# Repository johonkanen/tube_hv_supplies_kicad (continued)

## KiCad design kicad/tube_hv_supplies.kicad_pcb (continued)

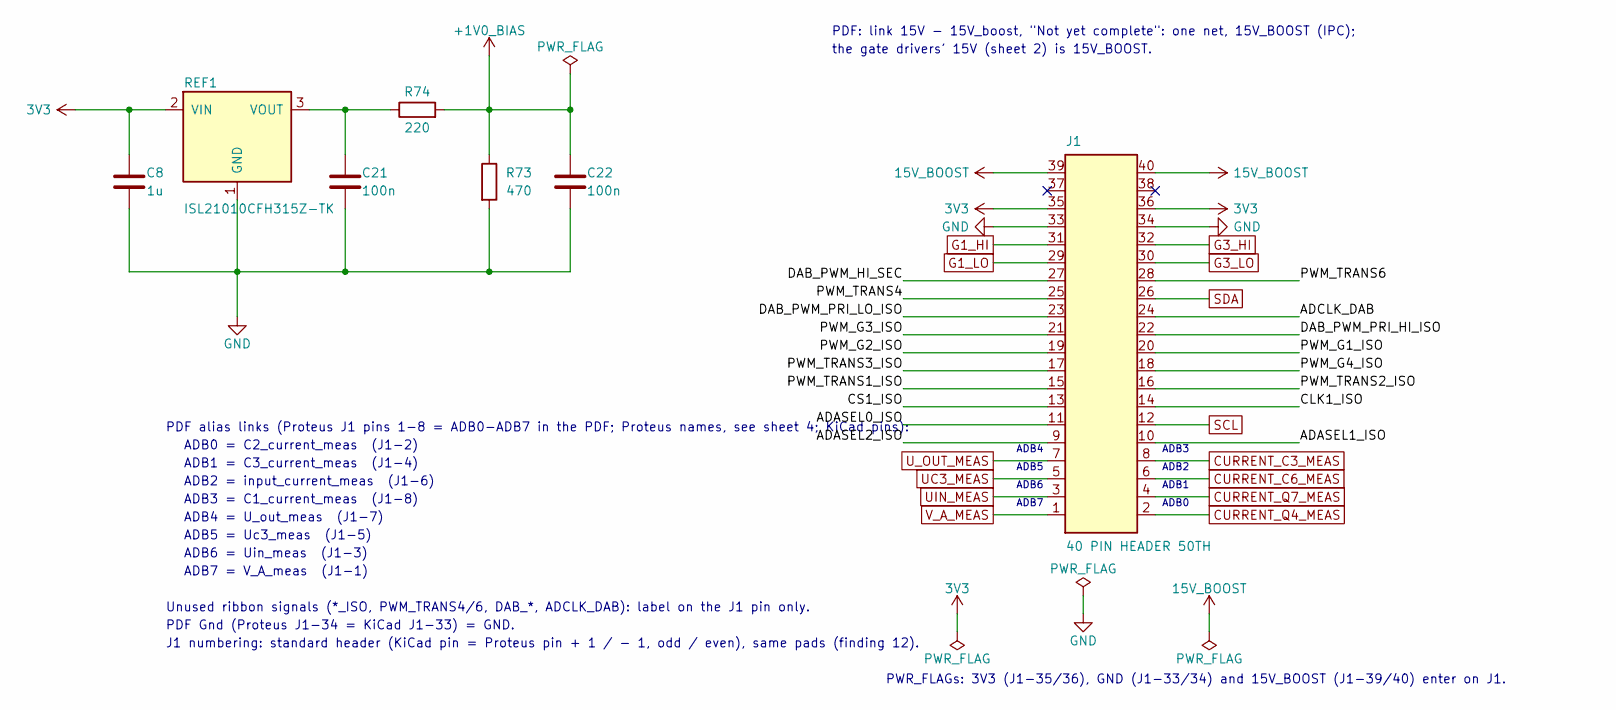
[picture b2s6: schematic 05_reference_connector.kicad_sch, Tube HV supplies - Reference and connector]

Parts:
C8: 1u; C_0603_1608Metric
C21, C22: 100n; C_0402_1005Metric
J1: 40 PIN HEADER 50TH; PinHeader_2x20_P1.27mm_Vertical_ProteusPads
R73: 470; R_0402_1005Metric_Proteus0.91
R74: 220; R_0402_1005Metric_Proteus0.91
REF1: ISL21010CFH315Z-TK; SOT-23_Proteus

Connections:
3V3: C8.1, J1.35, J1.36, REF1.2 (VIN); also elsewhere on the board
15V_BOOST: J1.39, J1.40; also elsewhere on the board
+1V0_BIAS: C22.1, R73.1, R74.2; also elsewhere on the board
/05 Reference and connector/ADASEL0_ISO: J1.11
/05 Reference and connector/ADASEL1_ISO: J1.10
/05 Reference and connector/ADASEL2_ISO: J1.9
/05 Reference and connector/ADCLK_DAB: J1.24
/05 Reference and connector/CLK1_ISO: J1.14
/05 Reference and connector/CS1_ISO: J1.13
/05 Reference and connector/DAB_PWM_HI_SEC: J1.27
/05 Reference and connector/DAB_PWM_PRI_HI_ISO: J1.22
/05 Reference and connector/DAB_PWM_PRI_LO_ISO: J1.23
/05 Reference and connector/PWM_G1_ISO: J1.20
/05 Reference and connector/PWM_G2_ISO: J1.19
/05 Reference and connector/PWM_G3_ISO: J1.21
/05 Reference and connector/PWM_G4_ISO: J1.18
/05 Reference and connector/PWM_TRANS1_ISO: J1.15
/05 Reference and connector/PWM_TRANS2_ISO: J1.16
/05 Reference and connector/PWM_TRANS3_ISO: J1.17
/05 Reference and connector/PWM_TRANS4: J1.25
/05 Reference and connector/PWM_TRANS6: J1.28
CURRENT_C3_MEAS: J1.8; also elsewhere on the board
CURRENT_C6_MEAS: J1.6; also elsewhere on the board
CURRENT_Q4_MEAS: J1.2; also elsewhere on the board
CURRENT_Q7_MEAS: J1.4; also elsewhere on the board
G1_HI: J1.31; also elsewhere on the board
G1_LO: J1.29; also elsewhere on the board
G3_HI: J1.32; also elsewhere on the board
G3_LO: J1.30; also elsewhere on the board
GND: C8.2, C21.2, C22.2, J1.33, J1.34, R73.2, REF1.1 (GND); also elsewhere on the board
unnamed: C21.1, R74.1, REF1.3 (VOUT)
SCL: J1.12; also elsewhere on the board
SDA: J1.26; also elsewhere on the board
UC3_MEAS: J1.5; also elsewhere on the board
UIN_MEAS: J1.3; also elsewhere on the board
U_OUT_MEAS: J1.7; also elsewhere on the board
V_A_MEAS: J1.1; also elsewhere on the board

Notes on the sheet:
ADB7
ADB0
ADB6
ADB1
ADB5
ADB2
ADB4
ADB3
PWR_FLAGs: 3V3 (J1-35/36), GND (J1-33/34) and 15V_BOOST (J1-39/40) enter on J1.
PDF: link 15V - 15V_boost, "Not yet complete": one net, 15V_BOOST (IPC);
the gate drivers' 15V (sheet 2) is 15V_BOOST.
PDF alias links (Proteus J1 pins 1-8 = ADB0-ADB7 in the PDF; Proteus names, see sheet 4; KiCad pins):
ADB0 = C2_current_meas (J1-2)
ADB1 = C3_current_meas (J1-4)
ADB2 = input_current_meas (J1-6)
ADB3 = C1_current_meas (J1-8)
ADB4 = U_out_meas (J1-7)
ADB5 = Uc3_meas (J1-5)
ADB6 = Uin_meas (J1-3)
ADB7 = V_A_meas (J1-1)
Unused ribbon signals (*_ISO, PWM_TRANS4/6, DAB_*, ADCLK_DAB): label on the J1 pin only.
PDF Gnd (Proteus J1-34 = KiCad J1-33) = GND.
J1 numbering: standard header (KiCad pin = Proteus pin + 1 / - 1, odd / even), same pads (finding 12).

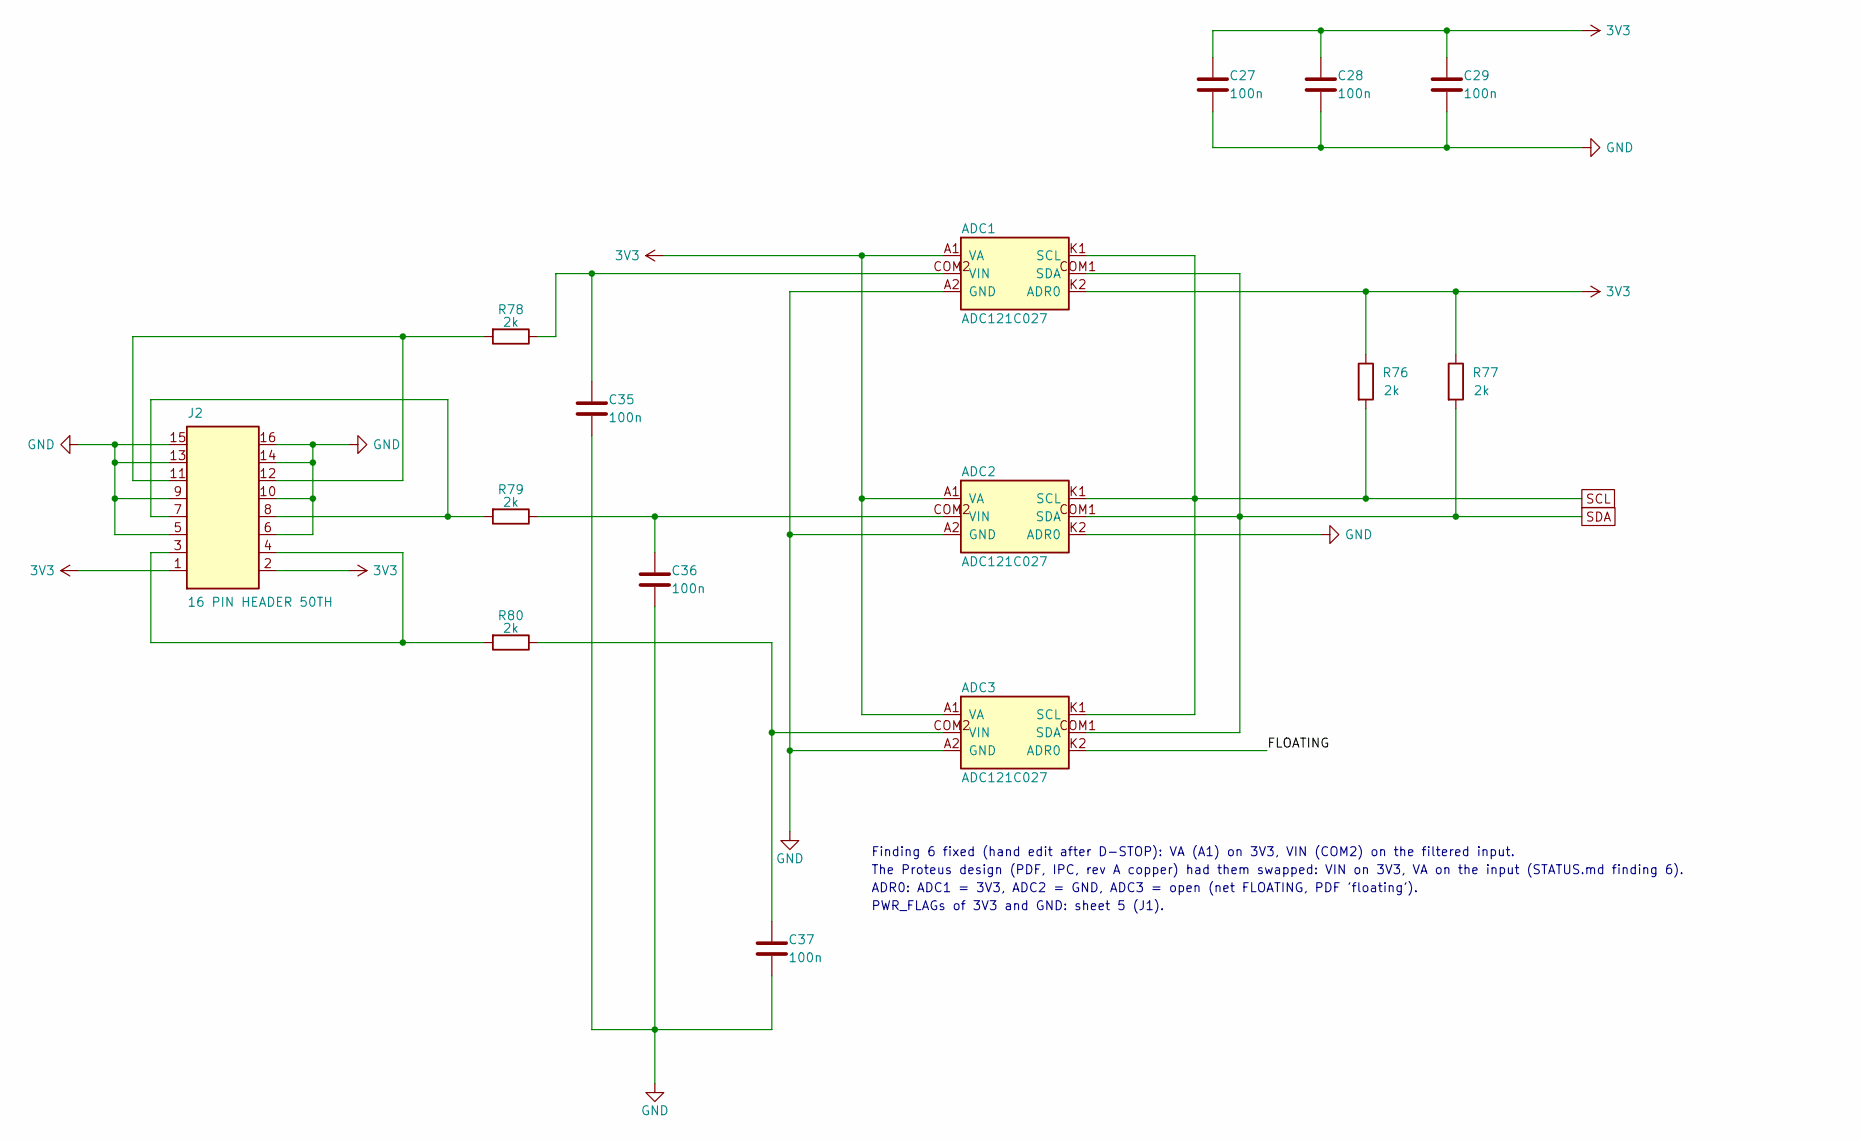
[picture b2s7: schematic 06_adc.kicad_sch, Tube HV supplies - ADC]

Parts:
ADC1, ADC2, ADC3: ADC121C027; SOT-23-6_ADC121C027_Proteus_ProteusPads
C27, C28, C29, C35, C36, C37: 100n; C_0603_1608Metric
J2: 16 PIN HEADER 50TH; PinHeader_2x08_P1.27mm_Vertical_ProteusPads
R76, R77, R78, R79, R80: 2k; R_0603_1608Metric

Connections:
3V3: ADC1.A1 (VA), ADC1.K2 (ADR0), ADC2.A1 (VA), ADC3.A1 (VA), C27.2, C28.2, C29.2, J2.1, J2.2, R76.1, R77.1; also elsewhere on the board
/06 ADC/FLOATING: ADC3.K2 (ADR0)
GND: ADC1.A2 (GND), ADC2.A2 (GND), ADC2.K2 (ADR0), ADC3.A2 (GND), C27.1, C28.1, C29.1, C35.1, C36.1, C37.1, J2.5, J2.6, J2.9, J2.10, J2.13, J2.14, J2.15, J2.16; also elsewhere on the board
unnamed: ADC1.COM2 (VIN), C35.2, R78.1
unnamed: ADC2.COM2 (VIN), C36.2, R79.1
unnamed: ADC3.COM2 (VIN), C37.2, R80.1
unnamed: J2.3, J2.4, R80.2
unnamed: J2.7, J2.8, R79.2
unnamed: J2.11, J2.12, R78.2
SCL: ADC1.K1 (SCL), ADC2.K1 (SCL), ADC3.K1 (SCL), R76.2; also elsewhere on the board
SDA: ADC1.COM1 (SDA), ADC2.COM1 (SDA), ADC3.COM1 (SDA), R77.2; also elsewhere on the board

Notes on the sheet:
Finding 6 fixed (hand edit after D-STOP): VA (A1) on 3V3, VIN (COM2) on the filtered input.
The Proteus design (PDF, IPC, rev A copper) had them swapped: VIN on 3V3, VA on the input (STATUS.md finding 6).
ADR0: ADC1 = 3V3, ADC2 = GND, ADC3 = open (net FLOATING, PDF 'floating').
PWR_FLAGs of 3V3 and GND: sheet 5 (J1).

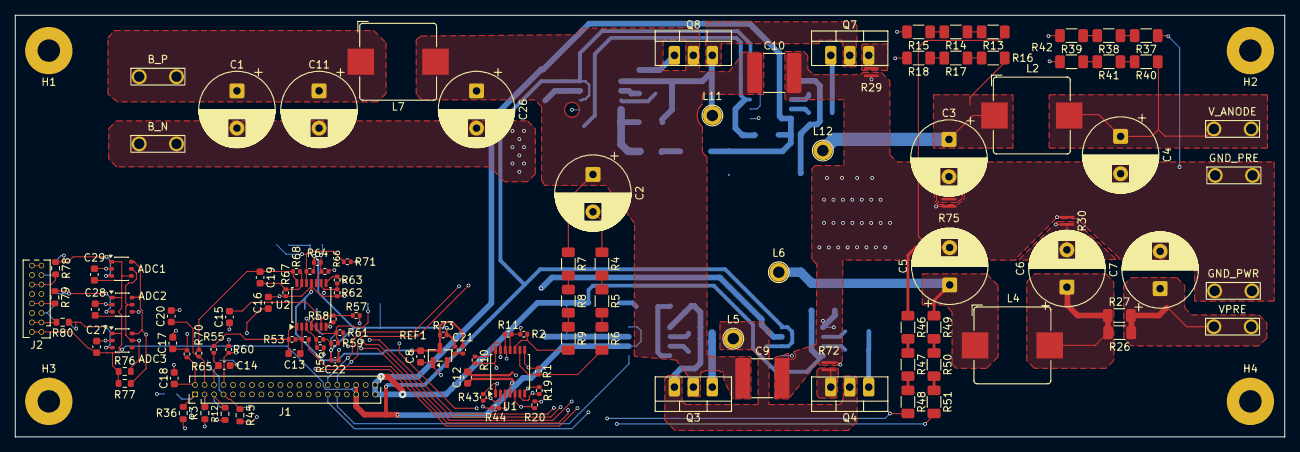
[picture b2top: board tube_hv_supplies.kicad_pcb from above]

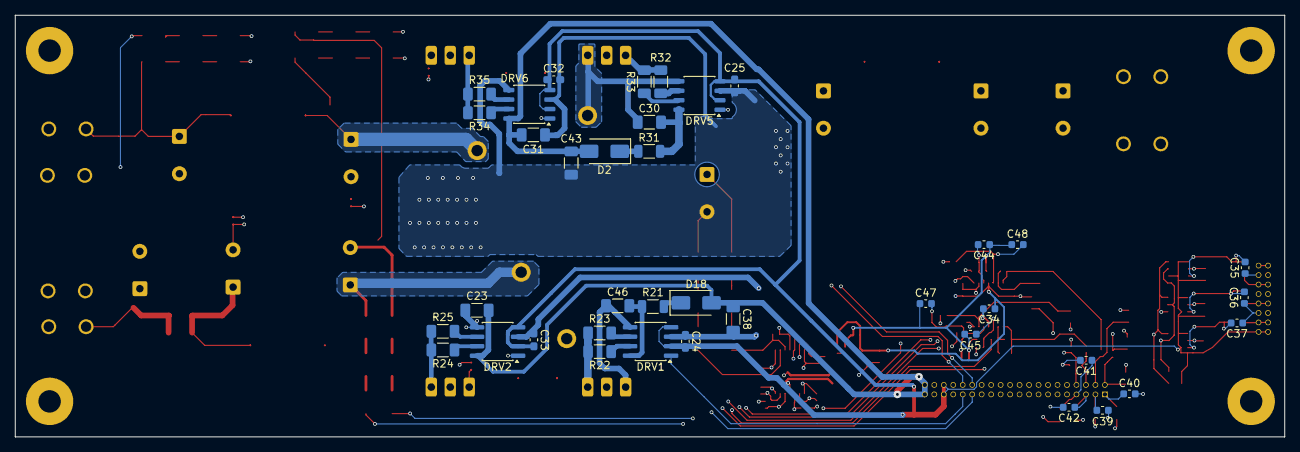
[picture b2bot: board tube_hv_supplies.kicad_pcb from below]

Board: 4 copper layers, 170.1 x 56.5 mm, 162 parts (38 on the bottom side), 94 nets.

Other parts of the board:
H1, H2, H3, H4: MountingHole_3.0mm; MountingHole_3.0mm_PTH_Pad6.35mm
